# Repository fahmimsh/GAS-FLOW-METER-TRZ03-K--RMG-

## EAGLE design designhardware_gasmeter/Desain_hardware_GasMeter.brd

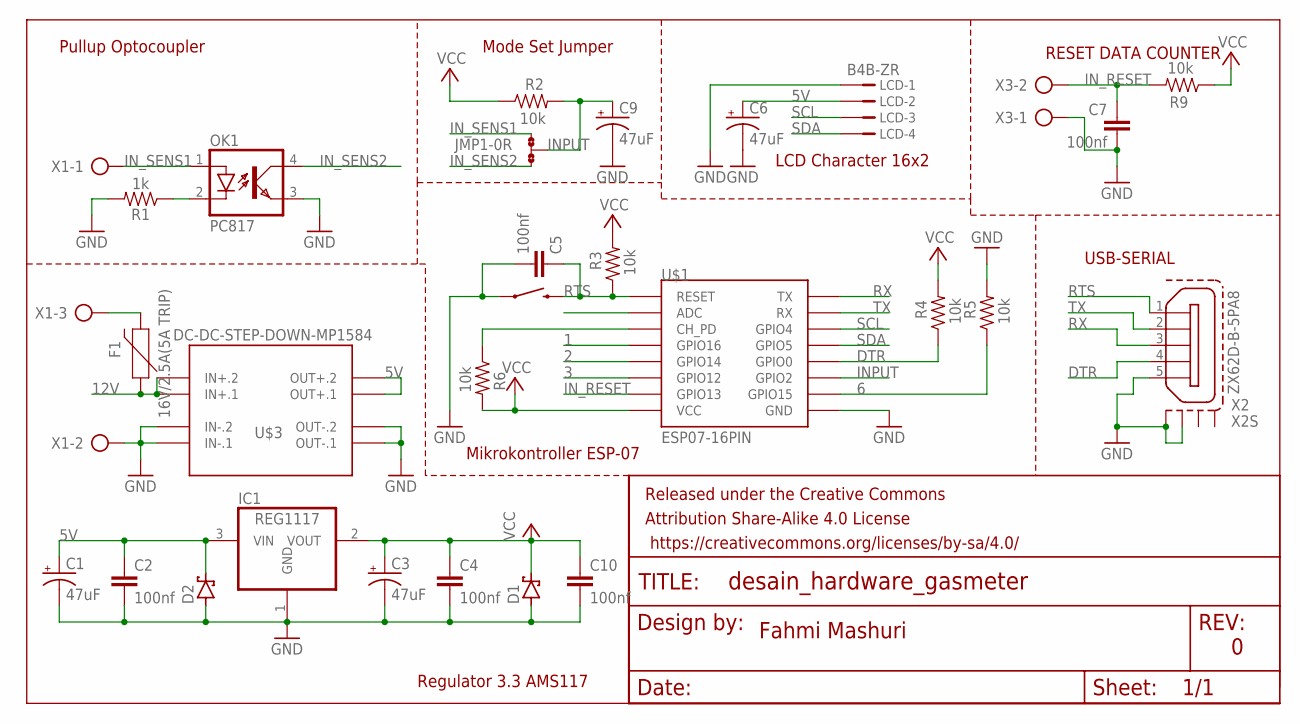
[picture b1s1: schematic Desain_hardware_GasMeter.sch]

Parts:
C1, C3, C6, C9: 47uF; EIA3528
C2, C4, C5, C7, C10: 100nf; 0805
D1, D2: SCHOTTKY-DIODESMD; SMB
F1: 16V/2.5A(5A TRIP); 1812
FRAME1: FRAME-LETTER; CREATIVE_COMMONS
IC1: REG1117; SOT223
JMP1: 0R-JUMPA; A0R-JMP
LCD: B4B-ZR
OK1: PC817; DIL04
R1: 1k; 1210
R2, R3, R4, R5, R6, R9: 10k; 0805
U$1: ESP07-16PIN
U$2: MOMENTARY-SWITCH-SPST-PTH-6.0MM; TACTILE_SWITCH_PTH_6.0MM
U$3: DC-DC-STEP-DOWN-MP1584
X1: AK500/3
X2: ZX62D-B-5PA8
X3: AK500/2

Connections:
1: U$1.GPIO16
2: U$1.GPIO14
3: U$1.GPIO12
5V: C1.A (+), C2.1, C6.A (+), D2.C, IC1.3 (VIN), LCD.2, U$3.OUT+.1, U$3.OUT+.2
6: R5.1, U$1.GPIO15
12V: F1.1, U$3.IN+.1, U$3.IN+.2
DTR: R4.1, U$1.GPIO0, X2.4
GND: C1.C (-), C2.2, C3.C (-), C4.2, C5.2, C6.C (-), C7.2, C9.C (-), C10.2, D1.A, D2.A, IC1.1 (GND), LCD.1, OK1.3 (EMIT), R1.2, R5.2, U$1.GND, U$2.1, U$3.IN-.1, U$3.IN-.2, U$3.OUT-.1, U$3.OUT-.2, X1.2, X2.5, X2.S1, X2.S2, X3.1
INPUT: C9.A (+), JMP1.2, R2.2, U$1.GPIO2
IN_RESET: C7.1, R9.2, U$1.GPIO13, X3.2
IN_SENS1: JMP1.1, OK1.1 (A), X1.1
IN_SENS2: JMP1.3, OK1.4 (COL)
unnamed: R6.1, U$1.CH_PD
unnamed: F1.2, X1.3
unnamed: OK1.2 (C), R1.1
RTS: C5.1, R3.1, U$1.REST (RESET), U$2.3 (2), X2.1
RX: U$1.TX, X2.3
SCL: LCD.3, U$1.GPIO4
SDA: LCD.4, U$1.GPIO5
TX: U$1.RX, X2.2
VCC: C3.A (+), C4.1, C10.1, D1.C, IC1.2 (VOUT), R2.1, R3.2, R4.2, R6.2, R9.1, U$1.VCC

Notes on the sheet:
USB-SERIAL
Mikrokontroller ESP-07
LCD Character 16x2
Regulator 3.3 AMS117
Fahmi Mashuri
RESET DATA COUNTER
Pullup Optocoupler
Mode Set Jumper

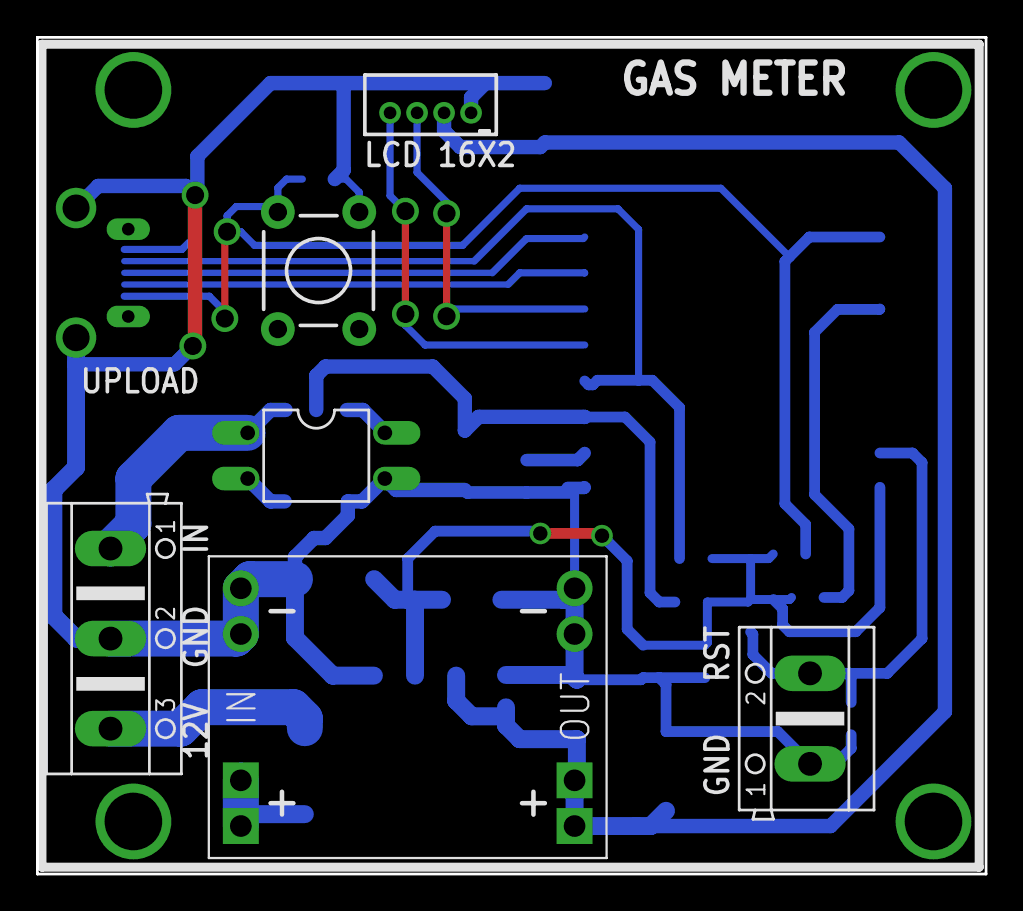
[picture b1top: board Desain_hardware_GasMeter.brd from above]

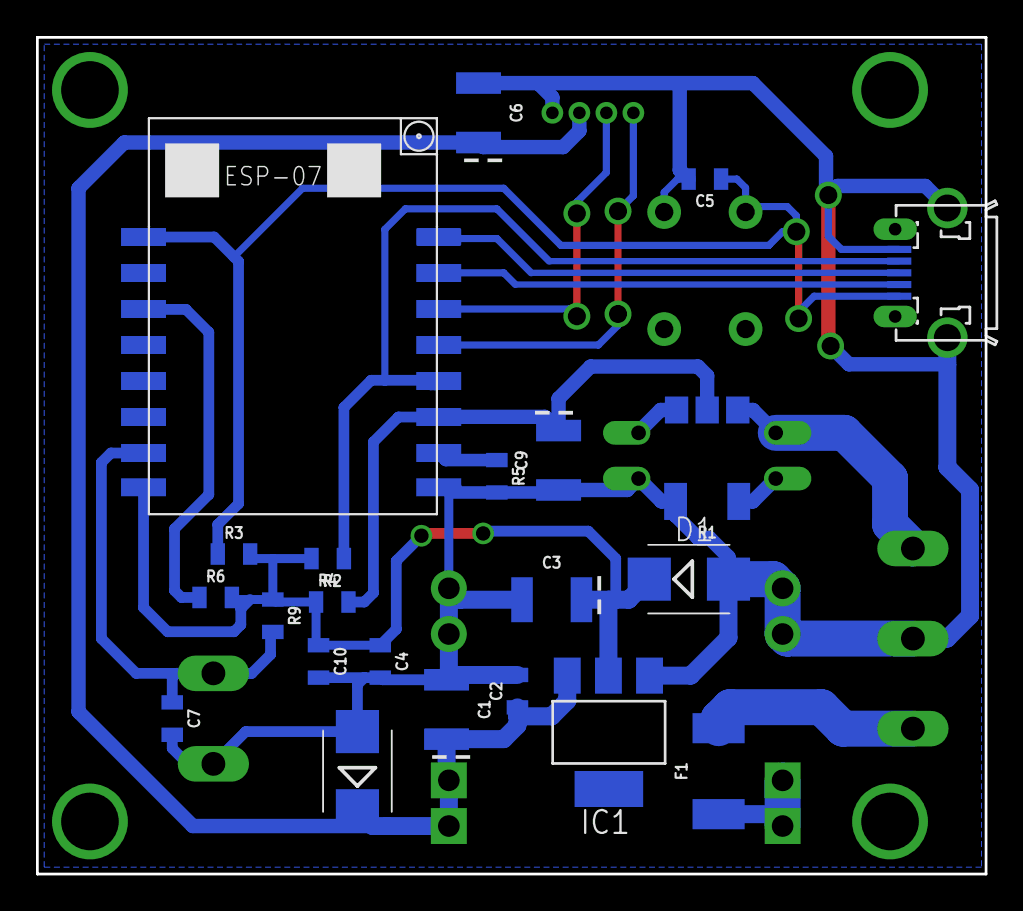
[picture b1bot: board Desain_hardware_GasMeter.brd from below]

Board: 2 copper layers, 52.7 x 46.5 mm, 30 parts (23 on the bottom side), 18 nets.

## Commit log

2022-05-12 upload

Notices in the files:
parts and their libraries:
SparkFun-Capacitors: Licensing: Creative Commons ShareAlike 4.0 International - https://creativecommons.org/licenses/by-sa/4.0
SparkFun-Aesthetics: Released under the Creative Commons Attribution Share-Alike 4.0 License
SparkFun-Aesthetics: https://creativecommons.org/licenses/by-sa/4.0
